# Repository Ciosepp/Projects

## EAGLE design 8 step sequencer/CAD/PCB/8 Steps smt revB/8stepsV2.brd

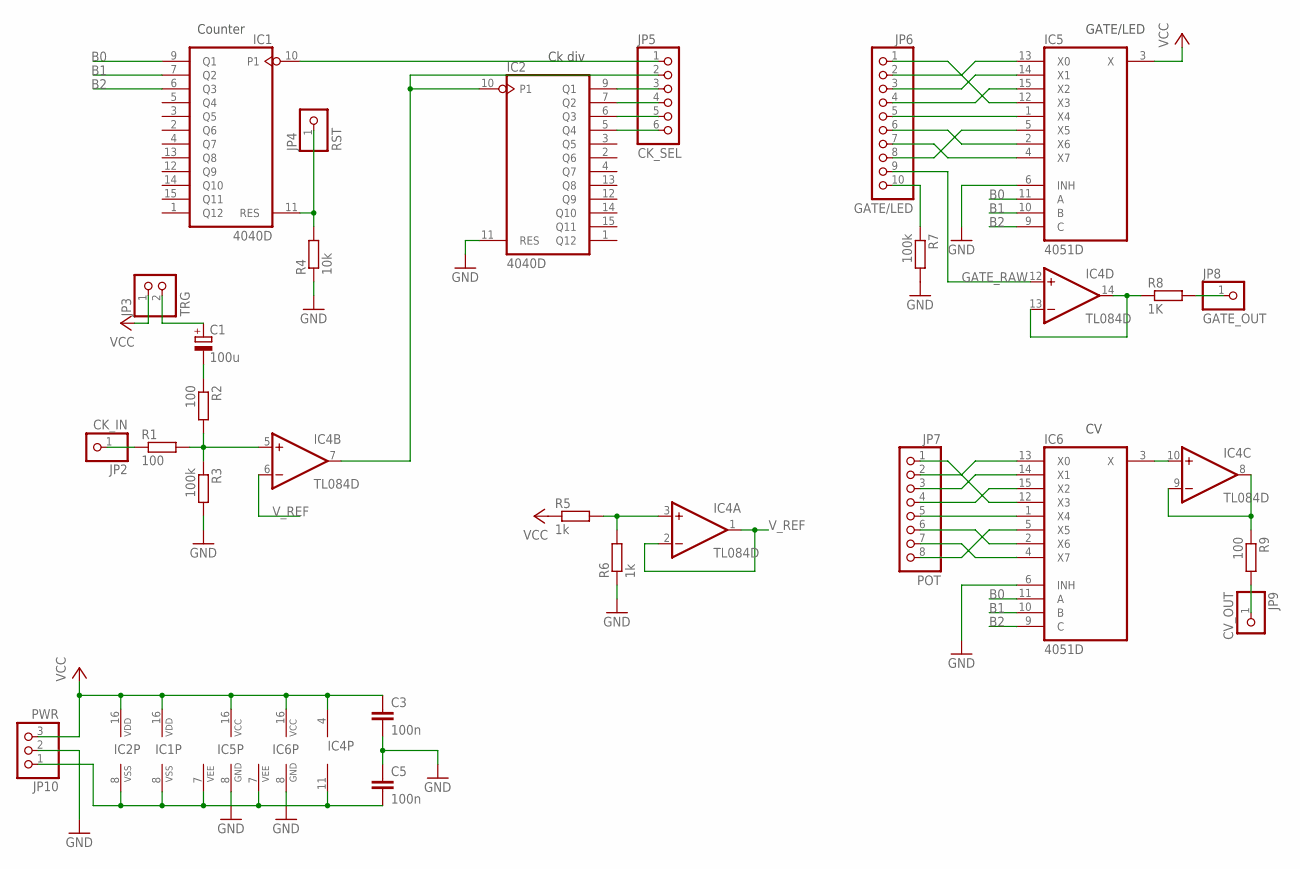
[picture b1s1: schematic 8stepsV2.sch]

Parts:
C1: 100u; E2,5-7
C3, C5: 100n; C025-024X044
IC1, IC2: 4040D; SO16
IC4: TL084D; SO14
IC5, IC6: 4051D; SO16
JP2: CK_IN; 1X01
JP3: TRG; 1X02
JP4: RST; 1X01
JP5: CK_SEL; 1X06
JP6: GATE/LED; 1X10
JP7: POT; 1X08
JP8: GATE_OUT; 1X01
JP9: CV_OUT; 1X01
JP10: PWR; 1X03
R1, R2, R9: 100; R0805
R3, R7: 100k; R0805
R4: 10k; R0805
R5, R6: 1k; R0805
R8: 1K; R0805

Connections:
B0: IC1.9 (Q1), IC5.11 (A), IC6.11 (A)
B1: IC1.7 (Q2), IC5.10 (B), IC6.10 (B)
B2: IC1.6 (Q3), IC5.9 (C), IC6.9 (C)
GATE_RAW: IC4.12 (+IN), JP6.9
GND: C3.2, C5.1, IC2.11 (RES), IC5.6 (INH), IC5.8 (GND), IC6.6 (INH), IC6.8 (GND), JP10.2, R3.2, R4.1, R6.1, R7.2
unnamed: IC4.3 (+IN), R5.2, R6.2
unnamed: C1.-, R2.1
unnamed: IC4.10 (+IN), IC6.3 (X)
unnamed: IC2.10 (P1), IC4.7 (OUT), JP5.2
unnamed: IC2.9 (Q1), JP5.3
unnamed: IC2.7 (Q2), JP5.4
unnamed: IC2.6 (Q3), JP5.5
unnamed: IC2.5 (Q4), JP5.6
unnamed: IC1.10 (P1), JP5.1
unnamed: IC5.12 (X3), JP6.1
unnamed: IC5.13 (X0), JP6.2
unnamed: IC5.14 (X1), JP6.3
unnamed: IC5.15 (X2), JP6.4
unnamed: IC5.1 (X4), JP6.5
unnamed: IC5.4 (X7), JP6.7
unnamed: IC5.2 (X6), JP6.6
unnamed: IC5.5 (X5), JP6.8
unnamed: IC6.12 (X3), JP7.1
unnamed: IC6.13 (X0), JP7.2
unnamed: IC6.14 (X1), JP7.3
unnamed: IC6.15 (X2), JP7.4
unnamed: IC6.1 (X4), JP7.5
unnamed: IC6.4 (X7), JP7.7
unnamed: IC6.5 (X5), JP7.8
unnamed: IC4.8 (OUT), IC4.9 (-IN), R9.1
unnamed: JP9.1, R9.2
unnamed: JP6.10, R7.1
unnamed: IC1.11 (RES), JP4.1, R4.2
unnamed: IC4.13 (-IN), IC4.14 (OUT), R8.1
unnamed: JP8.1, R8.2
unnamed: IC6.2 (X6), JP7.6
unnamed: IC4.5 (+IN), R1.2, R2.2, R3.1
unnamed: C1.+, JP3.2
unnamed: JP2.1, R1.1
VCC: C3.1, IC1.16 (VDD), IC2.16 (VDD), IC4.4 (V+), IC5.3 (X), IC5.16 (VCC), IC6.16 (VCC), JP3.1, JP10.3, R5.1
VSS: C5.2, IC1.8 (VSS), IC2.8 (VSS), IC4.11 (V-), IC5.7 (VEE), IC6.7 (VEE), JP10.1
V_REF: IC4.1 (OUT), IC4.2 (-IN), IC4.6 (-IN)

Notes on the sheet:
Ck div
Counter
GATE/LED

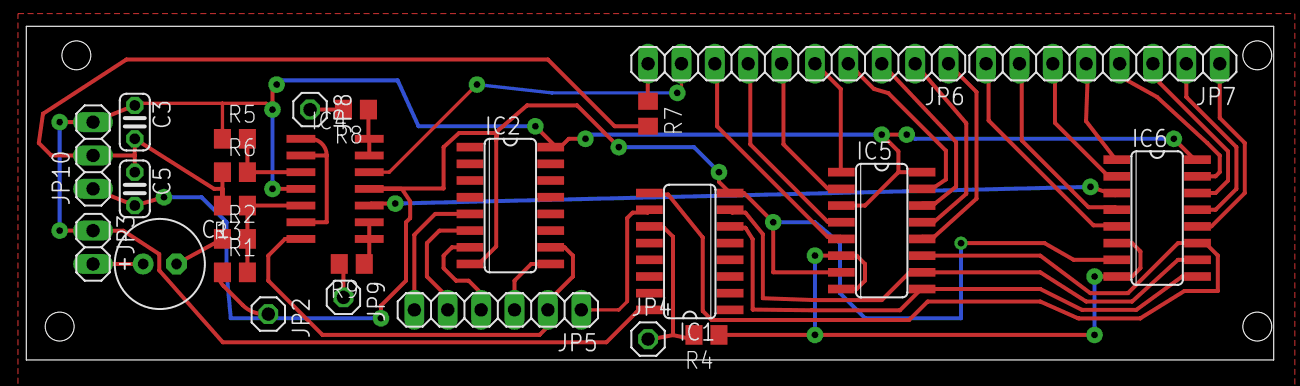
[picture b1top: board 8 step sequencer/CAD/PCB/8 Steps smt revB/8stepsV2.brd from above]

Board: 2 copper layers, 94.9 x 25.4 mm, 26 parts (0 on the bottom side), 42 nets.

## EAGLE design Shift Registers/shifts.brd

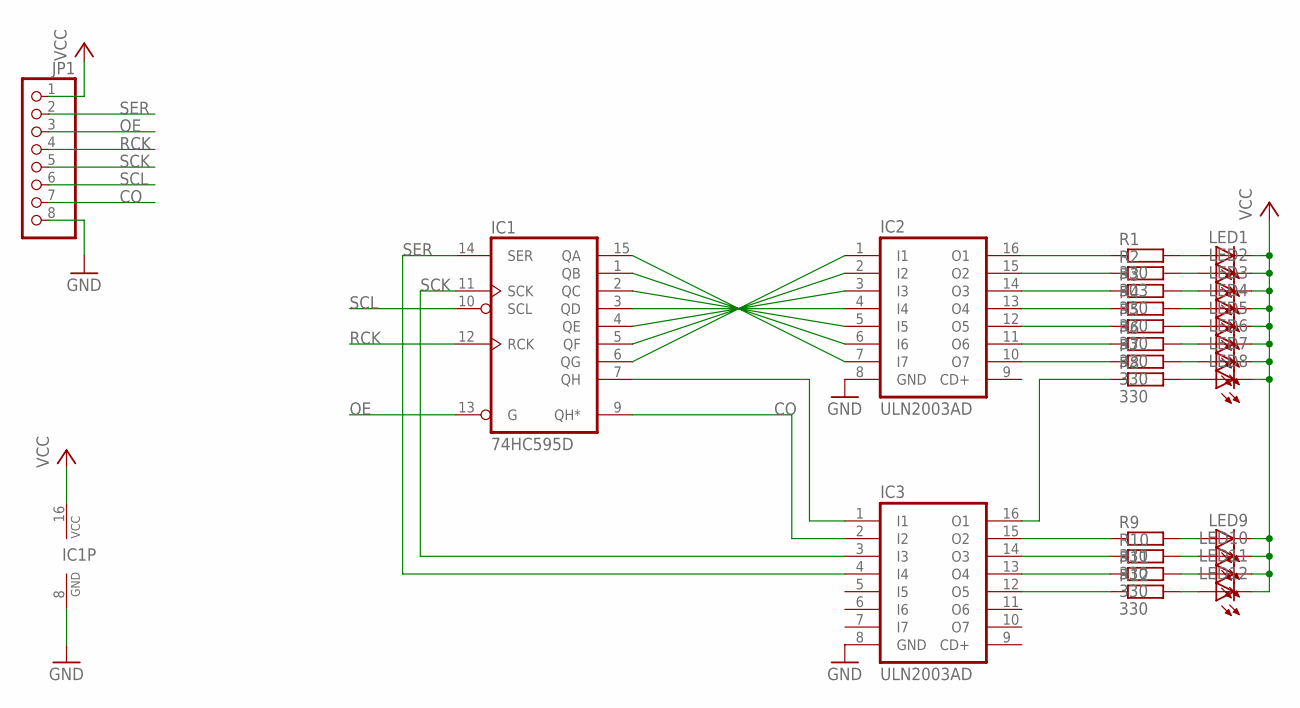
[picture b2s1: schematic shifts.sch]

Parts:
IC1: 74HC595D; SO16
IC2, IC3: ULN2003AD; SO16
JP1: PINHD-1X8BIG; 1X08-BIG
LED1, LED2, LED3, LED4, LED5, LED6, LED7, LED8, LED9, LED10, LED11, LED12: LEDCHIP-LED0805; CHIP-LED0805
R1, R3, R4, R5, R6, R7, R8, R9, R10, R11, R12: 330; R0805
R2: 303; R0805

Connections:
CO: IC1.9 (QH*), IC3.2 (I2), JP1.7
GND: IC1.8 (GND), IC2.8 (GND), IC3.8 (GND), JP1.8
unnamed: IC2.16 (O1), R1.1
unnamed: LED1.A, R1.2
unnamed: LED2.A, R2.2
unnamed: LED3.A, R3.2
unnamed: LED4.A, R4.2
unnamed: LED5.A, R5.2
unnamed: LED6.A, R6.2
unnamed: LED7.A, R7.2
unnamed: LED8.A, R8.2
unnamed: IC2.15 (O2), R2.1
unnamed: IC2.14 (O3), R3.1
unnamed: IC2.13 (O4), R4.1
unnamed: IC2.12 (O5), R5.1
unnamed: IC2.11 (O6), R6.1
unnamed: IC2.10 (O7), R7.1
unnamed: IC3.16 (O1), R8.1
unnamed: LED9.A, R9.2
unnamed: LED10.A, R10.2
unnamed: LED11.A, R11.2
unnamed: LED12.A, R12.2
unnamed: IC3.15 (O2), R9.1
unnamed: IC3.14 (O3), R10.1
unnamed: IC3.13 (O4), R11.1
unnamed: IC3.12 (O5), R12.1
unnamed: IC1.15 (QA), IC2.7 (I7)
unnamed: IC1.1 (QB), IC2.6 (I6)
unnamed: IC1.2 (QC), IC2.5 (I5)
unnamed: IC1.3 (QD), IC2.4 (I4)
unnamed: IC1.4 (QE), IC2.3 (I3)
unnamed: IC1.5 (QF), IC2.2 (I2)
unnamed: IC1.6 (QG), IC2.1 (I1)
unnamed: IC1.7 (QH), IC3.1 (I1)
OE: IC1.13 (G), JP1.3
RCK: IC1.12 (RCK), JP1.4
SCK: IC1.11 (SCK), IC3.3 (I3), JP1.5
SCL: IC1.10 (SCL), JP1.6
SER: IC1.14 (SER), IC3.4 (I4), JP1.2
VCC: IC1.16 (VCC), JP1.1, LED1.C, LED2.C, LED3.C, LED4.C, LED5.C, LED6.C, LED7.C, LED8.C, LED9.C, LED10.C, LED11.C, LED12.C

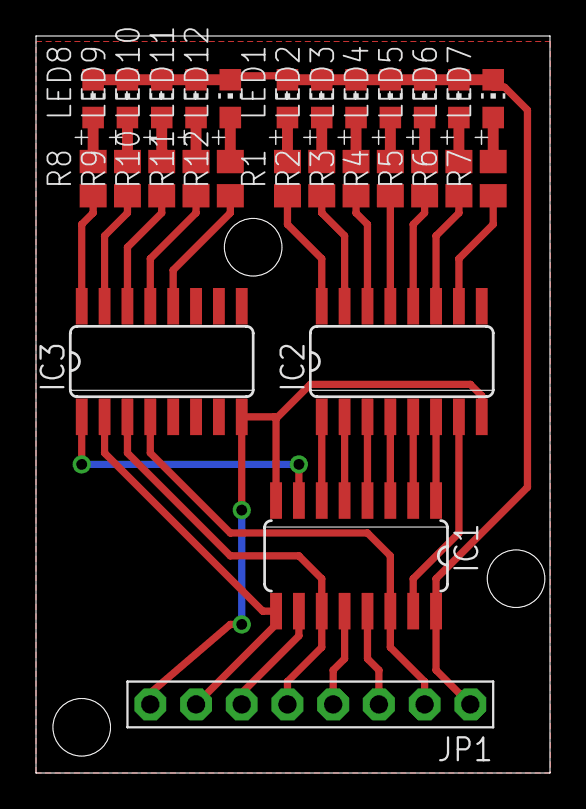
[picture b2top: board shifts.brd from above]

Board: 2 copper layers, 28.6 x 40.9 mm, 28 parts (0 on the bottom side), 40 nets.

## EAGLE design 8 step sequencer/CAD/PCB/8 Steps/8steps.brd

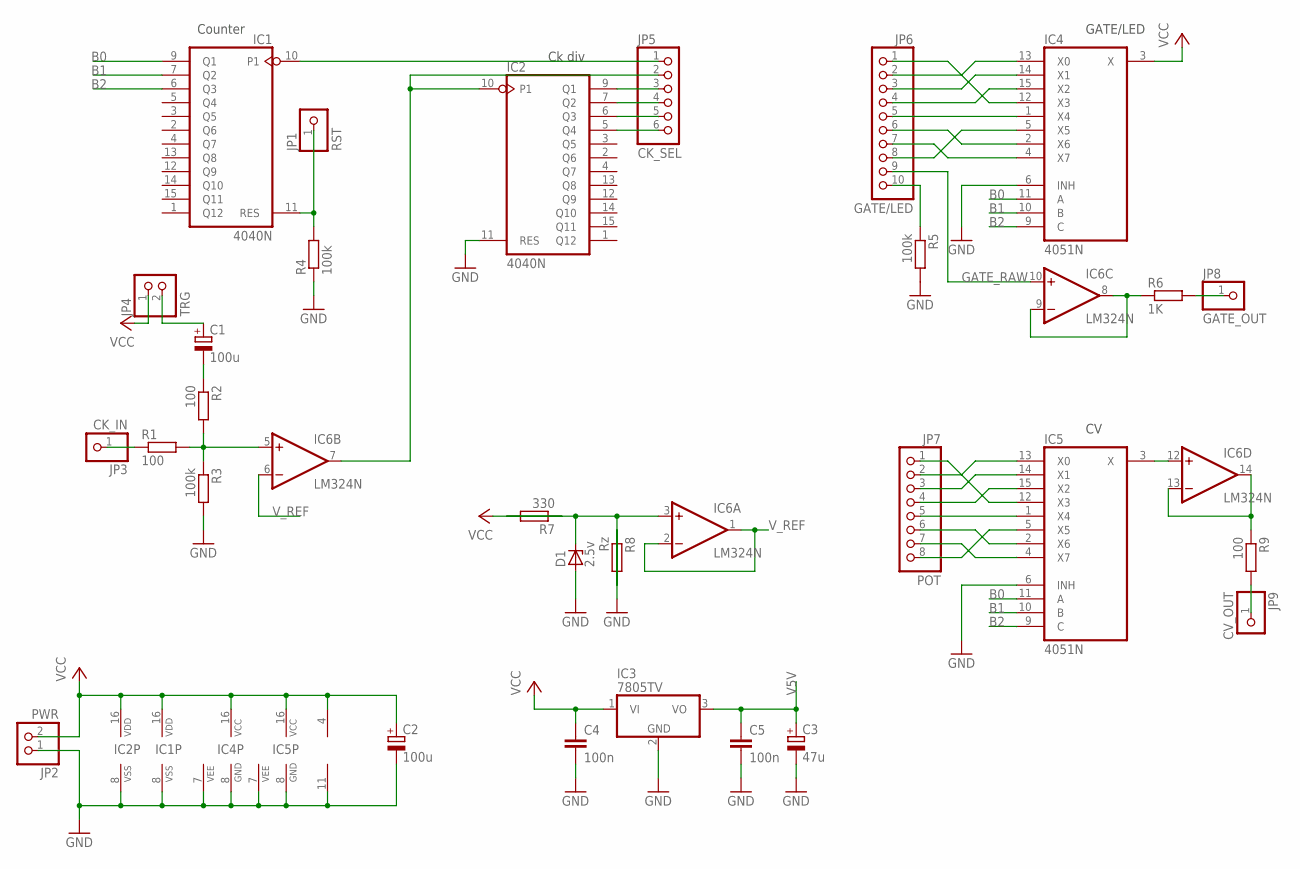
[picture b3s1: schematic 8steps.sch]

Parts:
C1, C2: 100u; E2,5-7
C3: 47u; E2,5-7
C4, C5: 100n; C050-025X075
D1: 2.5v; ZDIO-2.5
IC1, IC2: 4040N; DIL16
IC3: 7805TV; TO220V
IC4, IC5: 4051N; DIL16
IC6: LM324N; DIL14
JP1: RST; 1X01
JP2: PWR; 1X02
JP3: CK_IN; 1X01
JP4: TRG; 1X02
JP5: CK_SEL; 1X06
JP6: GATE/LED; 1X10
JP7: POT; 1X08
JP8: GATE_OUT; 1X01
JP9: CV_OUT; 1X01
R1, R2, R9: 100; 0207/2V
R3: 100k; 0204/7
R4, R5: 100k; 0207/2V
R6: 1K; 0207/2V
R7: 330; 0207/2V
R8: Rz; 0207/2V

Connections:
B0: IC1.9 (Q1), IC4.11 (A), IC5.11 (A)
B1: IC1.7 (Q2), IC4.10 (B), IC5.10 (B)
B2: IC1.6 (Q3), IC4.9 (C), IC5.9 (C)
GATE_RAW: IC6.10 (+IN), JP6.9
GND: C2.-, C3.-, C4.2, C5.2, D1.A, IC1.8 (VSS), IC2.8 (VSS), IC2.11 (RES), IC3.2 (GND), IC4.6 (INH), IC4.7 (VEE), IC4.8 (GND), IC5.6 (INH), IC5.7 (VEE), IC5.8 (GND), IC6.11 (V-), JP2.1, R3.2, R4.1, R5.2, R8.1
unnamed: D1.C, IC6.3 (+IN), R7.2, R8.2
unnamed: C1.-, R2.1
unnamed: IC5.3 (X), IC6.12 (+IN)
unnamed: IC2.10 (P1), IC6.7 (OUT), JP5.2
unnamed: IC2.9 (Q1), JP5.3
unnamed: IC2.7 (Q2), JP5.4
unnamed: IC2.6 (Q3), JP5.5
unnamed: IC2.5 (Q4), JP5.6
unnamed: IC1.10 (P1), JP5.1
unnamed: IC4.12 (X3), JP6.1
unnamed: IC4.13 (X0), JP6.2
unnamed: IC4.14 (X1), JP6.3
unnamed: IC4.15 (X2), JP6.4
unnamed: IC4.1 (X4), JP6.5
unnamed: IC4.4 (X7), JP6.7
unnamed: IC4.2 (X6), JP6.6
unnamed: IC4.5 (X5), JP6.8
unnamed: IC5.12 (X3), JP7.1
unnamed: IC5.13 (X0), JP7.2
unnamed: IC5.14 (X1), JP7.3
unnamed: IC5.15 (X2), JP7.4
unnamed: IC5.1 (X4), JP7.5
unnamed: IC5.4 (X7), JP7.7
unnamed: IC5.5 (X5), JP7.8
unnamed: IC6.13 (-IN), IC6.14 (OUT), R9.1
unnamed: JP9.1, R9.2
unnamed: JP6.10, R5.1
unnamed: IC1.11 (RES), JP1.1, R4.2
unnamed: IC6.8 (OUT), IC6.9 (-IN), R6.1
unnamed: JP8.1, R6.2
unnamed: IC5.2 (X6), JP7.6
unnamed: IC6.5 (+IN), R1.2, R2.2, R3.1
unnamed: C1.+, JP4.2
unnamed: JP3.1, R1.1
V5V: C3.+, C5.1, IC3.3 (VO)
VCC: C2.+, C4.1, IC1.16 (VDD), IC2.16 (VDD), IC3.1 (VI), IC4.3 (X), IC4.16 (VCC), IC5.16 (VCC), IC6.4 (V+), JP2.2, JP4.1, R7.1
V_REF: IC6.1 (OUT), IC6.2 (-IN), IC6.6 (-IN)

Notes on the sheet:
Ck div
Counter
GATE/LED

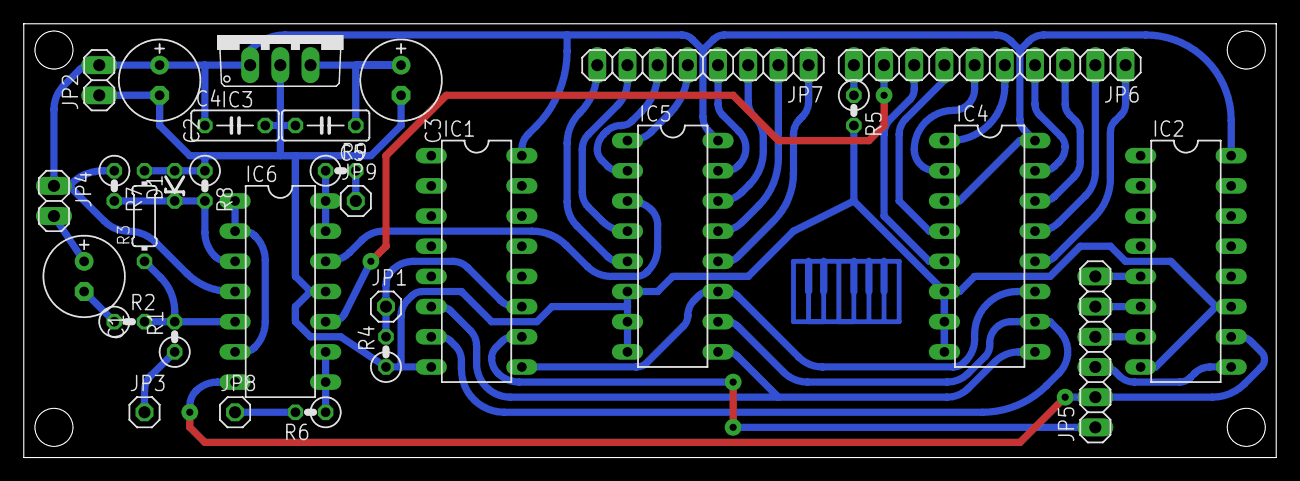
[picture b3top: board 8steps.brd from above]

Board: 2 copper layers, 105.4 x 36.5 mm, 30 parts (0 on the bottom side), 42 nets.

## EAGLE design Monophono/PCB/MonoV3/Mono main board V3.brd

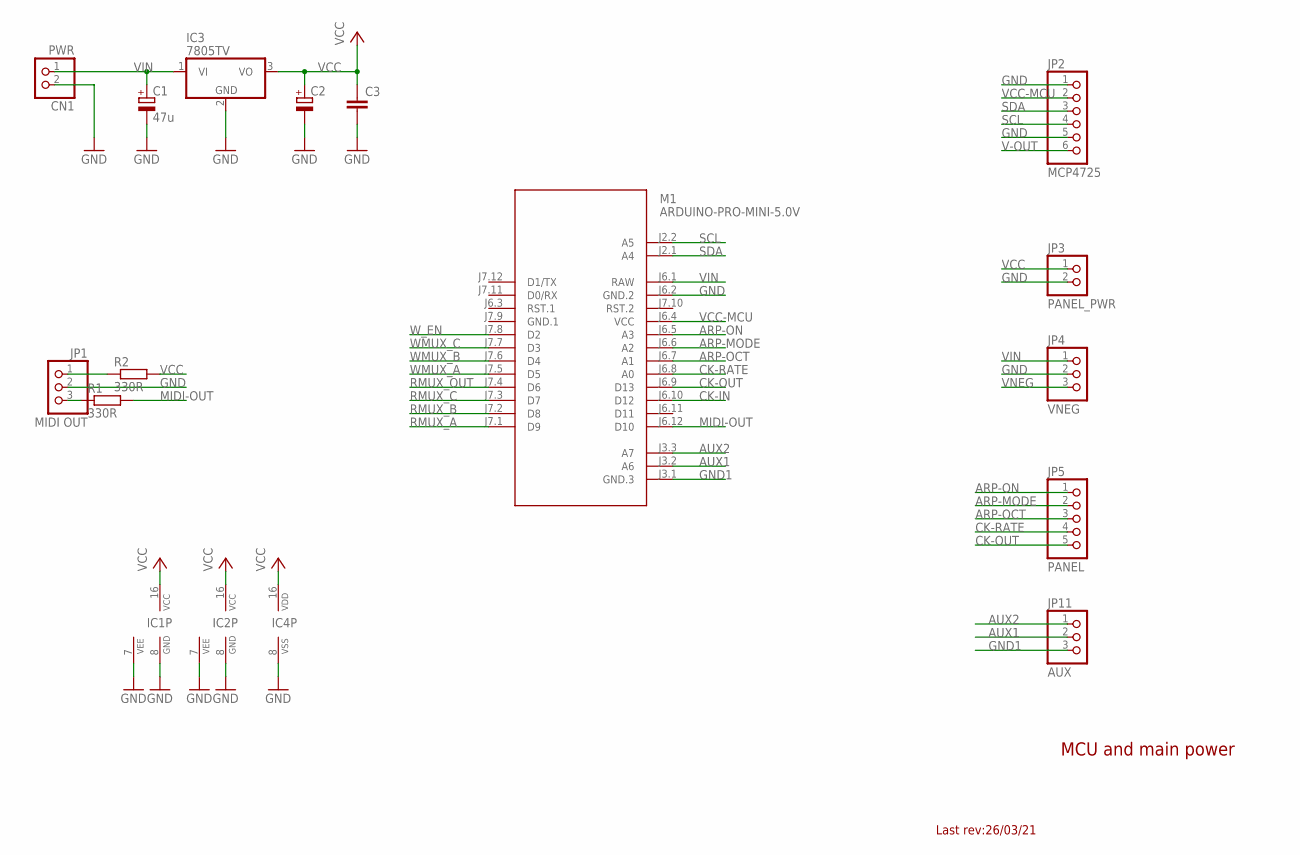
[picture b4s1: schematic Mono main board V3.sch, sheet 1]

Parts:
C1: 47u; E5-8,5
C2: CPOL-EUE5-8.5; E5-8,5
C3: C-EU050-025X075; C050-025X075
CN1: PWR; JST-PH-2-THM
IC1, IC2: 4051D; SO16
IC3: 7805TV; TO220V
IC4: 4040N; DIL16
JP1: MIDI OUT; 1X03
JP2: MCP4725; 1X06-CLEANBIG
JP3: PANEL_PWR; 1X02
JP4: VNEG; 1X03
JP5: PANEL; 1X05
JP11: AUX; 1X03
M1: ARDUINO-PRO-MINI-5.0V; ARDUINO-PRO-MINI#NP
R1, R2: 330R; R0805

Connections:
ARP-MODE: JP5.2, M1.J6.6 (A2)
ARP-OCT: JP5.3, M1.J6.7 (A1)
ARP-ON: JP5.1, M1.J6.5 (A3)
AUX1: JP11.2, M1.J3.2 (A6)
AUX2: JP11.1, M1.J3.3 (A7)
CK-IN: M1.J6.10 (D12); also elsewhere on the board
CK-OUT: JP5.5, M1.J6.9 (D13)
CK-RATE: JP5.4, M1.J6.8 (A0)
GND: C1.-, C2.-, C3.2, CN1.2 (1), IC1.7 (VEE), IC1.8 (GND), IC2.7 (VEE), IC2.8 (GND), IC3.2 (GND), IC4.8 (VSS), JP1.2, JP2.1, JP2.5, JP3.2, JP4.2, M1.J6.2 (GND.2); also elsewhere on the board
GND1: JP11.3, M1.J3.1 (GND.3)
GND.1: M1.J7.9 (GND.1)
MIDI-OUT: M1.J6.12 (D10), R1.2
unnamed: JP1.1, R2.1
unnamed: JP1.3, R1.1
RMUX_A: M1.J7.1 (D9); also elsewhere on the board
RMUX_B: M1.J7.2 (D8); also elsewhere on the board
RMUX_C: M1.J7.3 (D7); also elsewhere on the board
RMUX_OUT: M1.J7.4 (D6); also elsewhere on the board
SCL: JP2.4, M1.J2.2 (A5)
SDA: JP2.3, M1.J2.1 (A4)
V-OUT: JP2.6; also elsewhere on the board
VCC: C2.+, C3.1, IC1.16 (VCC), IC2.16 (VCC), IC3.3 (VO), IC4.16 (VDD), JP3.1, R2.2; also elsewhere on the board
VCC-MCU: JP2.2, M1.J6.4 (VCC)
VIN: C1.+, CN1.1 (2), IC3.1 (VI), JP4.1, M1.J6.1 (RAW); also elsewhere on the board
VNEG: JP4.3; also elsewhere on the board
WMUX_A: M1.J7.5 (D5); also elsewhere on the board
WMUX_B: M1.J7.6 (D4); also elsewhere on the board
WMUX_C: M1.J7.7 (D3); also elsewhere on the board
W_EN: M1.J7.8 (D2); also elsewhere on the board

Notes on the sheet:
MCU and main power
Last rev:26/03/21

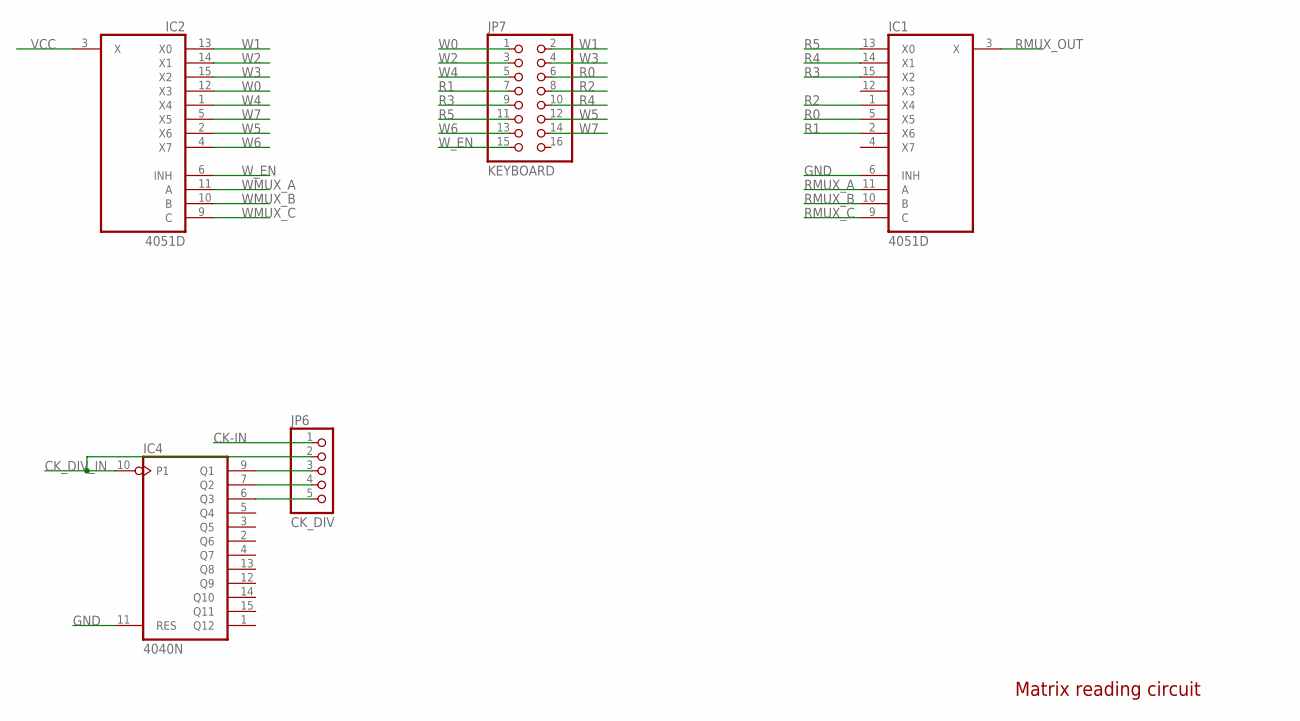
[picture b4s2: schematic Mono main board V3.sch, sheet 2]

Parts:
IC1, IC2: 4051D; SO16
IC4: 4040N; DIL16
JP6: CK_DIV; 1X05
JP7: KEYBOARD; 2X08

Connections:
CK-IN: JP6.1; also elsewhere on the board
CK_DIV_IN: IC4.10 (P1), JP6.2
GND: IC1.6 (INH), IC4.11 (RES); also elsewhere on the board
unnamed: IC4.9 (Q1), JP6.3
unnamed: IC4.7 (Q2), JP6.4
unnamed: IC4.6 (Q3), JP6.5
R0: IC1.5 (X5), JP7.6
R1: IC1.2 (X6), JP7.7
R2: IC1.1 (X4), JP7.8
R3: IC1.15 (X2), JP7.9
R4: IC1.14 (X1), JP7.10
R5: IC1.13 (X0), JP7.11
RMUX_A: IC1.11 (A); also elsewhere on the board
RMUX_B: IC1.10 (B); also elsewhere on the board
RMUX_C: IC1.9 (C); also elsewhere on the board
RMUX_OUT: IC1.3 (X); also elsewhere on the board
VCC: IC2.3 (X); also elsewhere on the board
W0: IC2.12 (X3), JP7.1
W1: IC2.13 (X0), JP7.2
W2: IC2.14 (X1), JP7.3
W3: IC2.15 (X2), JP7.4
W4: IC2.1 (X4), JP7.5
W5: IC2.2 (X6), JP7.12
W6: IC2.4 (X7), JP7.13
W7: IC2.5 (X5), JP7.14
WMUX_A: IC2.11 (A); also elsewhere on the board
WMUX_B: IC2.10 (B); also elsewhere on the board
WMUX_C: IC2.9 (C); also elsewhere on the board
W_EN: IC2.6 (INH), JP7.15; also elsewhere on the board

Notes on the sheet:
Matrix reading circuit

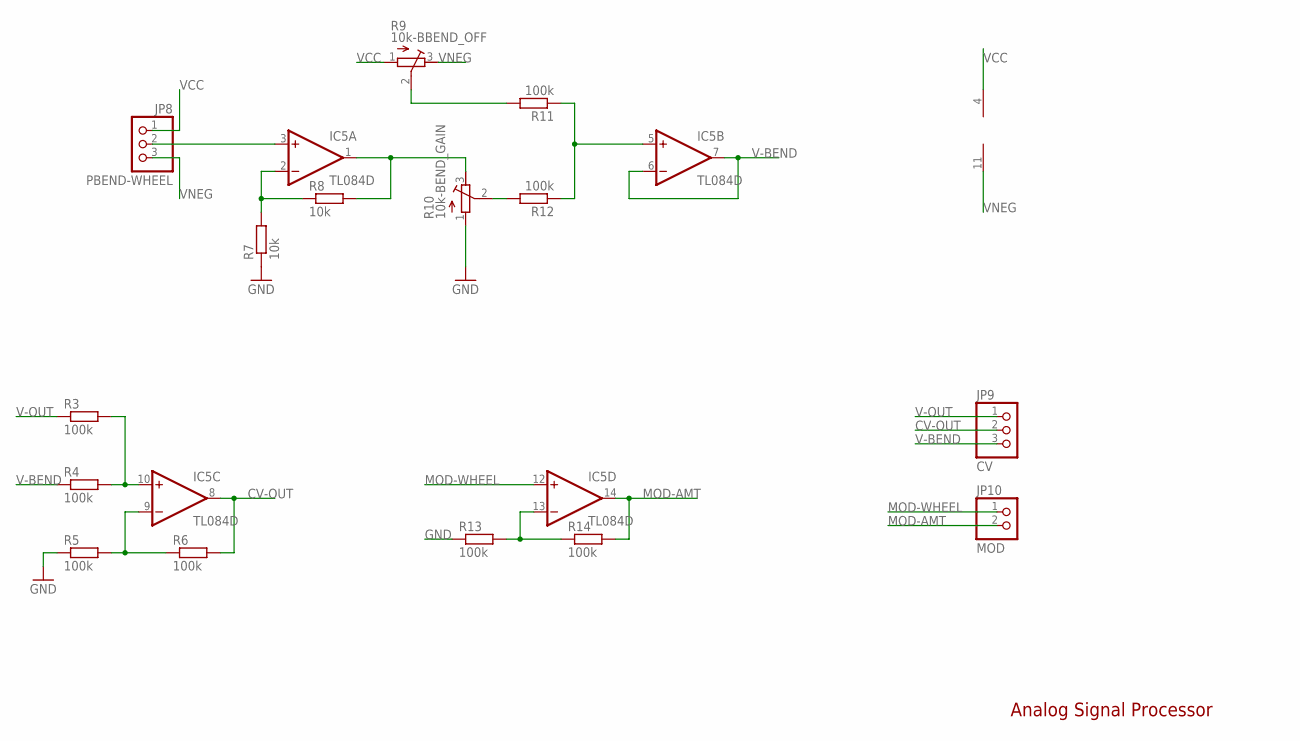
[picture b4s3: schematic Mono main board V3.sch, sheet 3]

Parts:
IC5: TL084D; SO14
JP8: PBEND-WHEEL; 1X03
JP9: CV; 1X03
JP10: MOD; 1X02
R3, R4, R5, R6, R11, R12, R13, R14: 100k; R0805
R7, R8: 10k; R0805
R9: 10k-BBEND_OFF; RTRIM64W
R10: 10k-BEND_GAIN; RTRIM64W

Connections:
CV-OUT: IC5.8 (OUT), JP9.2, R6.2
GND: R5.1, R7.1, R10.1 (A), R13.1; also elsewhere on the board
MOD-AMT: IC5.14 (OUT), JP10.2, R14.2
MOD-WHEEL: IC5.12 (+IN), JP10.1
unnamed: IC5.10 (+IN), R3.2, R4.2
unnamed: IC5.9 (-IN), R5.2, R6.1
unnamed: IC5.3 (+IN), JP8.2
unnamed: IC5.2 (-IN), R7.2, R8.1
unnamed: R10.2 (S), R12.2
unnamed: R9.2 (S), R11.2
unnamed: IC5.5 (+IN), R11.1, R12.1
unnamed: IC5.13 (-IN), R13.2, R14.1
unnamed: IC5.1 (OUT), R8.2, R10.3 (E)
V-BEND: IC5.6 (-IN), IC5.7 (OUT), JP9.3, R4.1
V-OUT: JP9.1, R3.1; also elsewhere on the board
VCC: IC5.4 (V+), JP8.1, R9.1 (A); also elsewhere on the board
VNEG: IC5.11 (V-), JP8.3, R9.3 (E); also elsewhere on the board

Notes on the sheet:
Analog Signal Processor

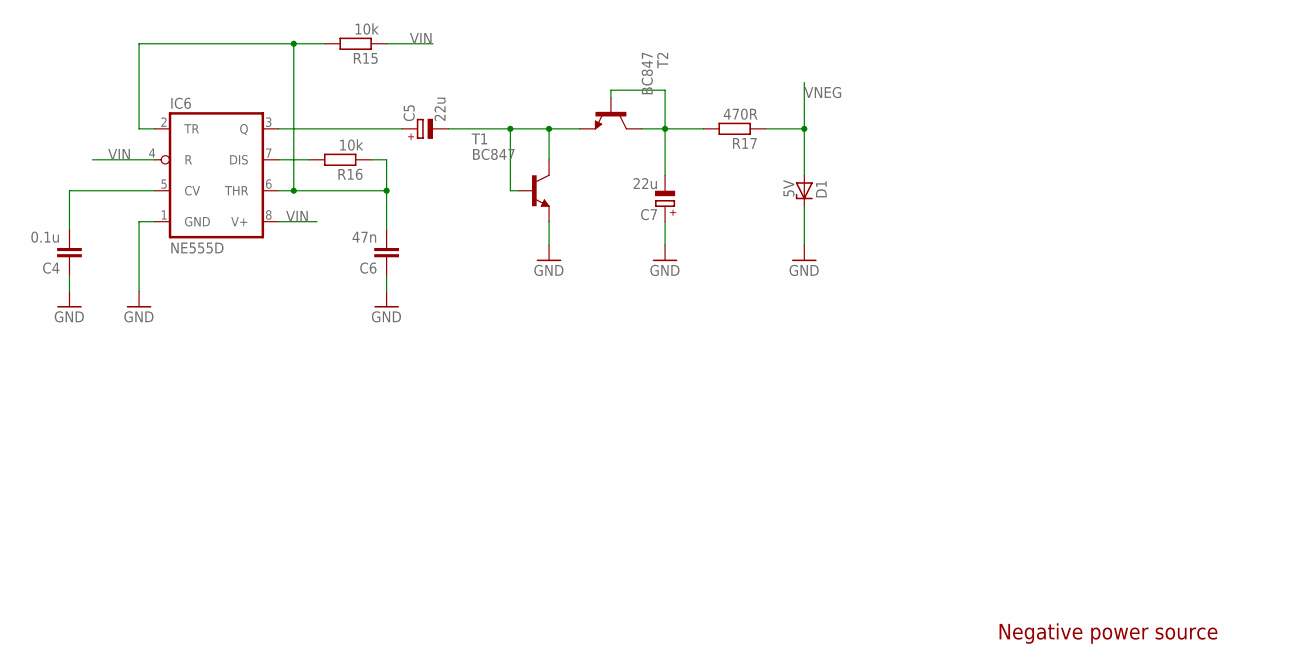
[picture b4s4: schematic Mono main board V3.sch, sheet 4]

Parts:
C4: 0.1u; C0805
C5, C7: 22u; E5-10,5
C6: 47n; C0805
D1: 5V; ZDIO-2.5
IC6: NE555D; SO08
R15, R16: 10k; M0805
R17: 470R; M0805
T1, T2: BC847; SOT23

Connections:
GND: C4.1, C6.1, C7.+, D1.C, IC6.1 (GND), T1.2 (E); also elsewhere on the board
unnamed: C4.2, IC6.5 (CV)
unnamed: C6.2, IC6.2 (TR), IC6.6 (THR), R15.2, R16.1
unnamed: IC6.7 (DIS), R16.2
unnamed: C5.+, IC6.3 (Q)
unnamed: C7.-, R17.2, T2.1 (B), T2.3 (C)
unnamed: C5.-, T1.1 (B), T1.3 (C), T2.2 (E)
VIN: IC6.4 (R), IC6.8 (V+), R15.1; also elsewhere on the board
VNEG: D1.A, R17.1; also elsewhere on the board

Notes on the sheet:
Negative power source

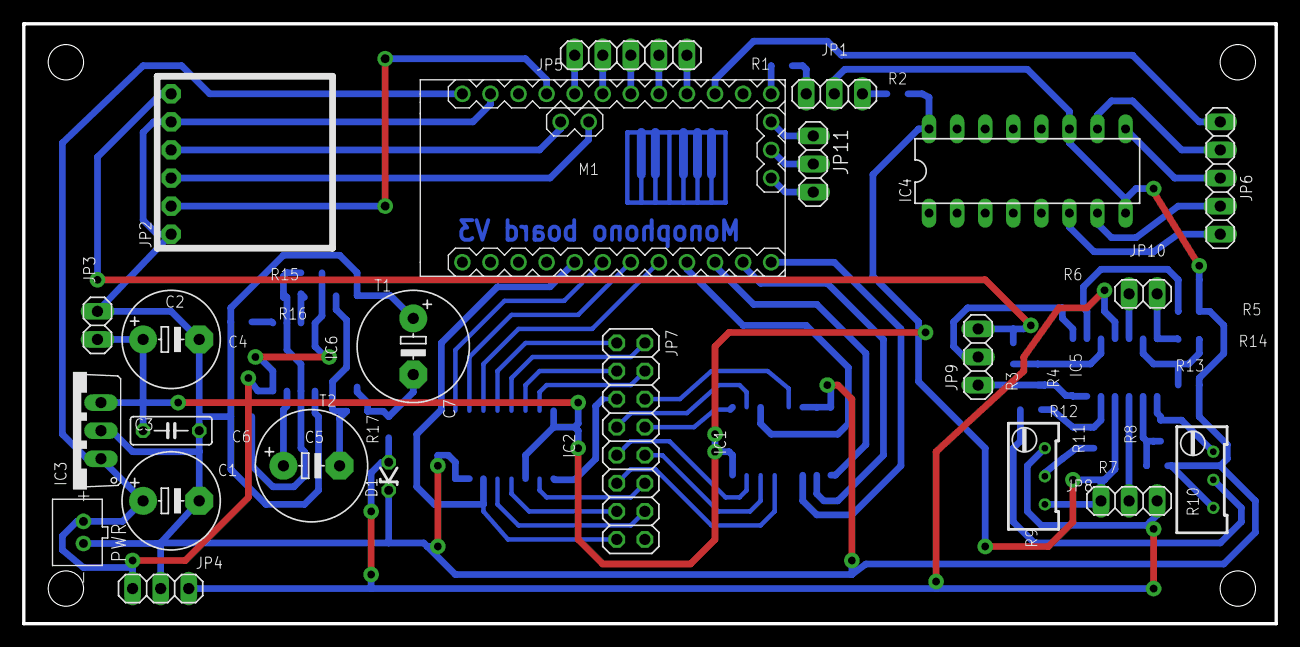
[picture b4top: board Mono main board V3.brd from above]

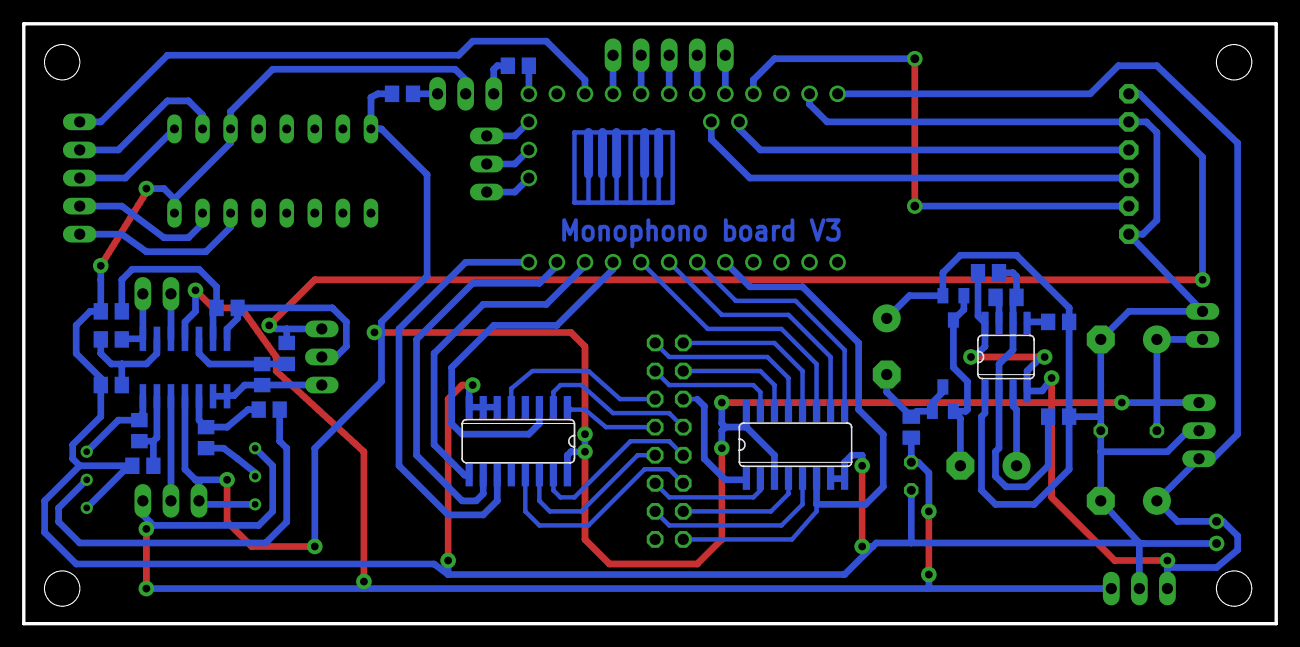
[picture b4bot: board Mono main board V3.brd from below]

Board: 2 copper layers, 113.3 x 54.3 mm, 46 parts (23 on the bottom side), 65 nets.

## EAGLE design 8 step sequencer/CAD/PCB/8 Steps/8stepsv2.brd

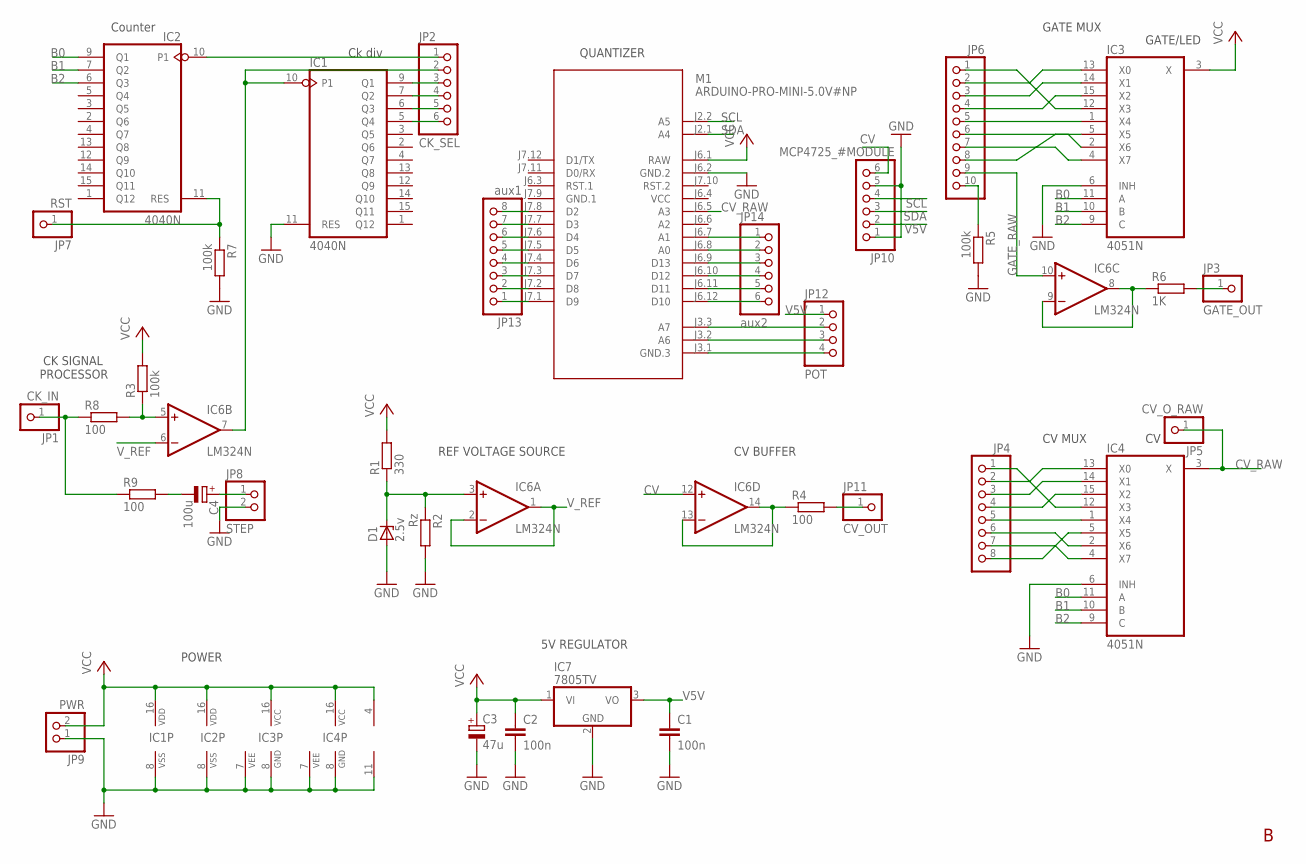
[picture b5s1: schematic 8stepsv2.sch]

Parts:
C1, C2: 100n; C050-025X075
C3: 47u; E2,5-7
C4: 100u; E2,5-7
D1: 2.5v; ZDIO-2.5
IC1, IC2: 4040N; DIL16
IC3, IC4: 4051N; DIL16
IC6: LM324N; DIL14
IC7: 7805TV; TO220V
JP1: CK_IN; 1X01
JP2: CK_SEL; 1X06
JP3: GATE_OUT; 1X01
JP4: PINHD-1X8; 1X08
JP5: CV_O_RAW; 1X01
JP6: PINHD-1X10; 1X10
JP7: RST; 1X01
JP8: STEP; 1X02
JP9: PWR; 1X02
JP10: MCP4725_#MODULE; 1X06
JP11: CV_OUT; 1X01
JP12: POT; 1X04
JP13: aux1; 1X08
JP14: aux2; 1X06
M1: ARDUINO-PRO-MINI-5.0V#NP; ARDUINO-PRO-MINI#NP
R1: 330; 0207/2V
R2: Rz; 0207/2V
R3, R5, R7: 100k; 0207/2V
R4, R8, R9: 100; 0207/2V
R6: 1K; 0207/2V

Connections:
B0: IC2.9 (Q1), IC3.11 (A), IC4.11 (A)
B1: IC2.7 (Q2), IC3.10 (B), IC4.10 (B)
B2: IC2.6 (Q3), IC3.9 (C), IC4.9 (C)
CV: IC6.12 (+IN), JP10.6
CV_RAW: IC4.3 (X), JP5.1, M1.J6.5 (A3)
GATE_RAW: IC6.10 (+IN), JP6.9
GND: C1.2, C2.2, C3.-, D1.A, IC1.8 (VSS), IC1.11 (RES), IC2.8 (VSS), IC3.6 (INH), IC3.7 (VEE), IC3.8 (GND), IC4.6 (INH), IC4.7 (VEE), IC4.8 (GND), IC6.11 (V-), IC7.2 (GND), JP8.2, JP9.1, JP10.1, JP10.5, JP12.4, M1.J3.1 (GND.3), M1.J6.2 (GND.2), R2.2, R5.2, R7.2
GND.1: M1.J7.9 (GND.1)
unnamed: D1.C, IC6.3 (+IN), R1.1, R2.1
unnamed: JP1.1, R8.1, R9.1
unnamed: JP13.1, M1.J7.1 (D9)
unnamed: IC1.10 (P1), IC6.7 (OUT), JP2.2
unnamed: IC1.9 (Q1), JP2.3
unnamed: IC1.7 (Q2), JP2.4
unnamed: IC1.6 (Q3), JP2.5
unnamed: IC1.5 (Q4), JP2.6
unnamed: IC2.10 (P1), JP2.1
unnamed: IC3.12 (X3), JP6.1
unnamed: IC3.13 (X0), JP6.2
unnamed: IC3.14 (X1), JP6.3
unnamed: IC3.15 (X2), JP6.4
unnamed: IC3.2 (X6), JP6.6
unnamed: IC3.5 (X5), JP6.8
unnamed: IC3.4 (X7), JP6.7
unnamed: IC3.1 (X4), JP6.5
unnamed: IC4.12 (X3), JP4.1
unnamed: IC4.13 (X0), JP4.2
unnamed: IC4.14 (X1), JP4.3
unnamed: IC4.15 (X2), JP4.4
unnamed: IC4.1 (X4), JP4.5
unnamed: IC4.2 (X6), JP4.6
unnamed: IC4.4 (X7), JP4.7
unnamed: IC4.5 (X5), JP4.8
unnamed: IC6.13 (-IN), IC6.14 (OUT), R4.1
unnamed: JP11.1, R4.2
unnamed: JP6.10, R5.1
unnamed: IC2.11 (RES), JP7.1, R7.1
unnamed: IC6.8 (OUT), IC6.9 (-IN), R6.1
unnamed: JP3.1, R6.2
unnamed: C4.-, R9.2
unnamed: IC6.5 (+IN), R3.1, R8.2
unnamed: C4.+, JP8.1
unnamed: JP12.3, M1.J3.2 (A6)
unnamed: JP12.2, M1.J3.3 (A7)
unnamed: JP13.2, M1.J7.2 (D8)
unnamed: JP13.3, M1.J7.3 (D7)
unnamed: JP13.4, M1.J7.4 (D6)
unnamed: JP13.5, M1.J7.5 (D5)
unnamed: JP13.6, M1.J7.6 (D4)
unnamed: JP13.7, M1.J7.7 (D3)
unnamed: JP13.8, M1.J7.8 (D2)
unnamed: JP14.1, M1.J6.7 (A1)
unnamed: JP14.2, M1.J6.8 (A0)
unnamed: JP14.3, M1.J6.9 (D13)
unnamed: JP14.4, M1.J6.10 (D12)
unnamed: JP14.5, M1.J6.11 (D11)
unnamed: JP14.6, M1.J6.12 (D10)
SCL: JP10.4, M1.J2.2 (A5)
SDA: JP10.3, M1.J2.1 (A4)
V5V: C1.1, IC7.3 (VO), JP10.2, JP12.1
VCC: C2.1, C3.+, IC1.16 (VDD), IC2.16 (VDD), IC3.3 (X), IC3.16 (VCC), IC4.16 (VCC), IC6.4 (V+), IC7.1 (VI), JP9.2, M1.J6.1 (RAW), M1.J6.4 (VCC), R1.2, R3.2
V_REF: IC6.1 (OUT), IC6.2 (-IN), IC6.6 (-IN)

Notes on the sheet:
Ck div
Counter
GATE/LED
POWER
5V REGULATOR
REF VOLTAGE SOURCE
CV BUFFER
CV MUX
GATE MUX
QUANTIZER
CK SIGNAL PROCESSOR

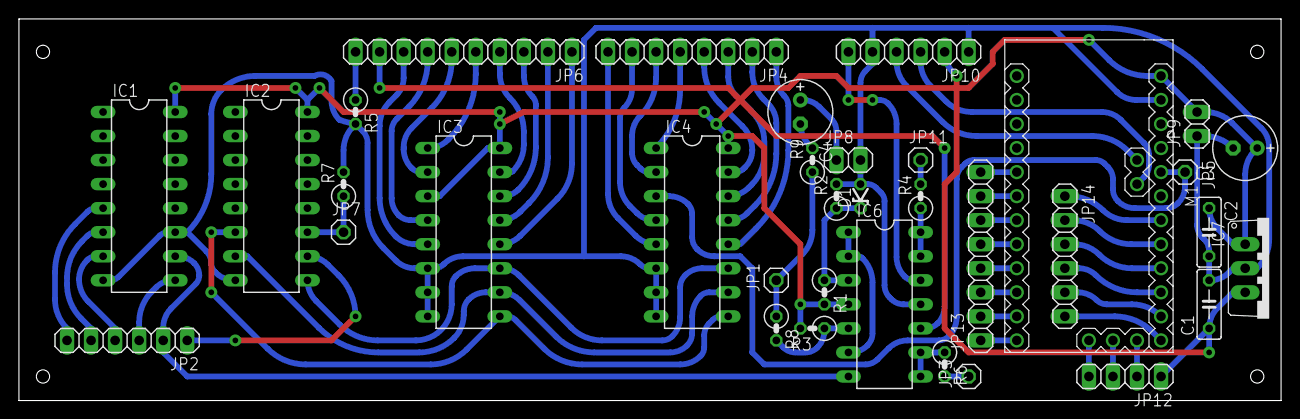
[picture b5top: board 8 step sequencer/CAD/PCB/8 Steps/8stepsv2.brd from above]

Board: 2 copper layers, 133.3 x 40.3 mm, 35 parts (0 on the bottom side), 61 nets.

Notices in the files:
parts and their libraries:
diy-modules: Released under the Creative Commons Attribution 4.0 International License: http://creativecommons.org/licenses/by/4.0
